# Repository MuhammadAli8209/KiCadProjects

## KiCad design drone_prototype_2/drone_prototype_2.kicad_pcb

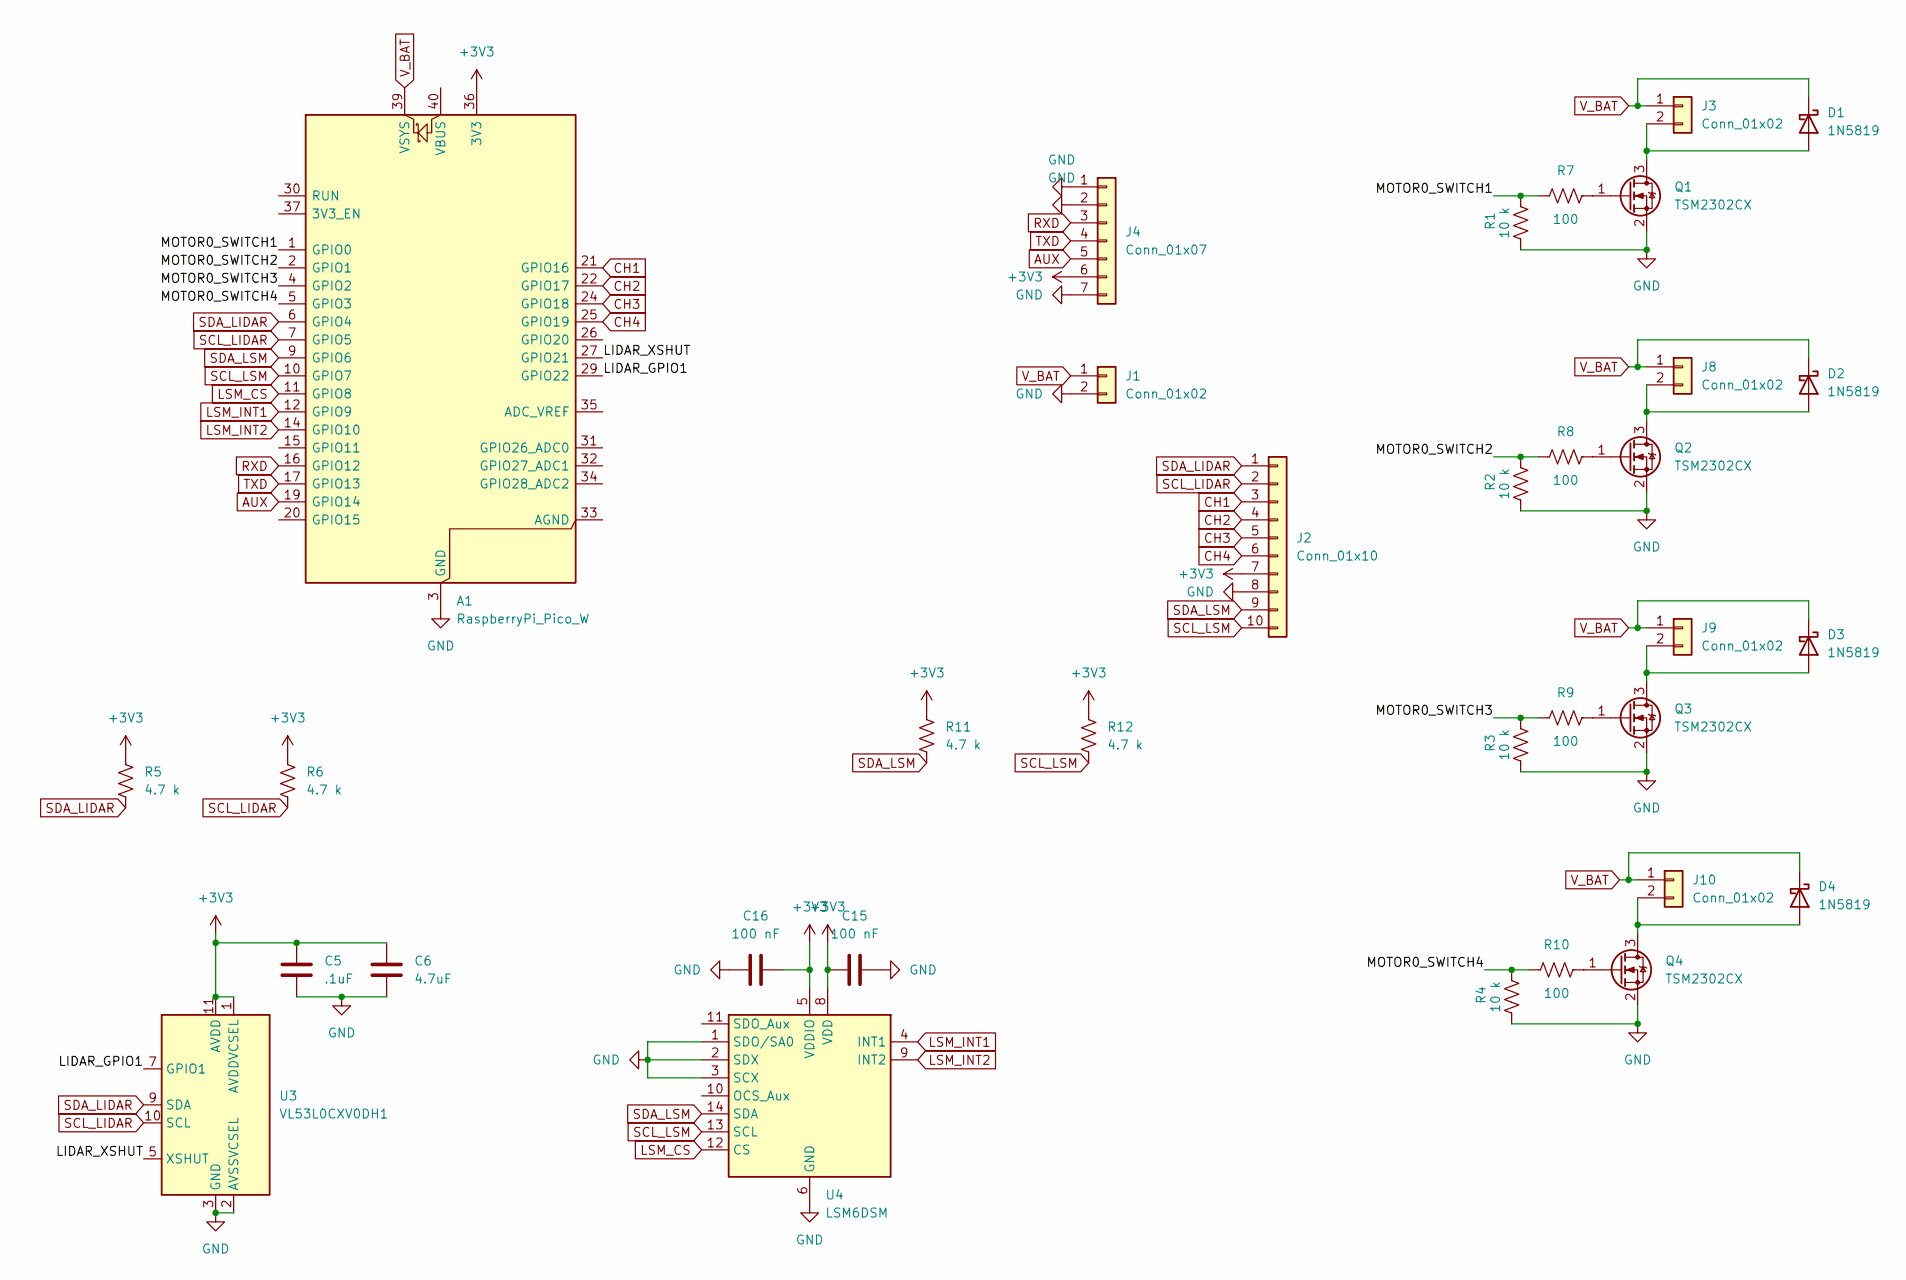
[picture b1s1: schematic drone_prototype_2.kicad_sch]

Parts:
A1: RaspberryPi_Pico_W; RaspberryPi_Pico_Common_Unspecified
C5: .1uF; C_0603_1608Metric
C6: 4.7uF; C_0603_1608Metric
C15, C16: 100 nF; C_0603_1608Metric
D1, D2, D3, D4: 1N5819; D_DO-41_SOD81_P10.16mm_Horizontal
J1, J3, J8, J9, J10: Conn_01x02; JST_PH_B2B-PH-K_1x02_P2.00mm_Vertical
J2: Conn_01x10; PinHeader_1x10_P2.54mm_Vertical
J4: Conn_01x07; PinHeader_1x07_P2.54mm_Vertical
Q1, Q2, Q3, Q4: TSM2302CX; SOT-23
R1, R2, R3, R4: 10 k; R_0603_1608Metric
R5, R6, R11, R12: 4.7 k; R_0603_1608Metric
R7, R8, R9, R10: 100; R_0603_1608Metric
U3: VL53L0CXV0DH1; ST_VL53L1x
U4: LSM6DSM; LGA-14_3x2.5mm_P0.5mm_LayoutBorder3x4y

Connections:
+3V3: A1.36 (3V3), C5.1, C6.1, C15.1, C16.2, J2.7, J4.6, R5.1, R6.1, R11.1, R12.1, U3.1 (AVDDVCSEL), U3.11 (AVDD), U4.5 (VDDIO), U4.8 (VDD)
/LIDAR_GPIO1: A1.29 (GPIO22), U3.7 (GPIO1)
/LIDAR_XSHUT: A1.27 (GPIO21), U3.5 (XSHUT)
/MOTOR0_SWITCH1: A1.1 (GPIO0), R1.2, R7.1
/MOTOR0_SWITCH2: A1.2 (GPIO1), R2.2, R8.1
/MOTOR0_SWITCH3: A1.4 (GPIO2), R3.2, R9.1
/MOTOR0_SWITCH4: A1.5 (GPIO3), R4.2, R10.1
AUX: A1.19 (GPIO14), J4.5
CH1: A1.21 (GPIO16), J2.3
CH2: A1.22 (GPIO17), J2.4
CH3: A1.24 (GPIO18), J2.5
CH4: A1.25 (GPIO19), J2.6
GND: A1.3 (GND), A1.8 (GND), A1.13 (GND), A1.18 (GND), A1.23 (GND), A1.28 (GND), A1.38 (GND), C5.2, C6.2, C15.2, C16.1, J1.2, J2.8, J4.1, J4.2, J4.7, Q1.2 (S), Q2.2 (S), Q3.2 (S), Q4.2 (S), R1.1, R2.1, R3.1, R4.1, U3.2 (AVSSVCSEL), U3.3 (GND), U3.4 (GND), U3.6 (GND), U3.12 (GND), U4.1 (SDO/SA0), U4.2 (SDX), U4.3 (SCX), U4.6 (GND), U4.7 (GND)
LSM_CS: A1.11 (GPIO8), U4.12 (CS)
LSM_INT1: A1.12 (GPIO9), U4.4 (INT1)
LSM_INT2: A1.14 (GPIO10), U4.9 (INT2)
unnamed: D1.2 (A), J3.2, Q1.3 (D)
unnamed: D2.2 (A), J8.2, Q2.3 (D)
unnamed: D3.2 (A), J9.2, Q3.3 (D)
unnamed: D4.2 (A), J10.2, Q4.3 (D)
unnamed: Q1.1 (G), R7.2
unnamed: Q2.1 (G), R8.2
unnamed: Q3.1 (G), R9.2
unnamed: Q4.1 (G), R10.2
RXD: A1.16 (GPIO12), J4.3
SCL_LIDAR: A1.7 (GPIO5), J2.2, R6.2, U3.10 (SCL)
SCL_LSM: A1.10 (GPIO7), J2.10, R12.2, U4.13 (SCL)
SDA_LIDAR: A1.6 (GPIO4), J2.1, R5.2, U3.9 (SDA)
SDA_LSM: A1.9 (GPIO6), J2.9, R11.2, U4.14 (SDA)
TXD: A1.17 (GPIO13), J4.4
V_BAT: A1.39 (VSYS), D1.1 (K), D2.1 (K), D3.1 (K), D4.1 (K), J1.1, J3.1, J8.1, J9.1, J10.1

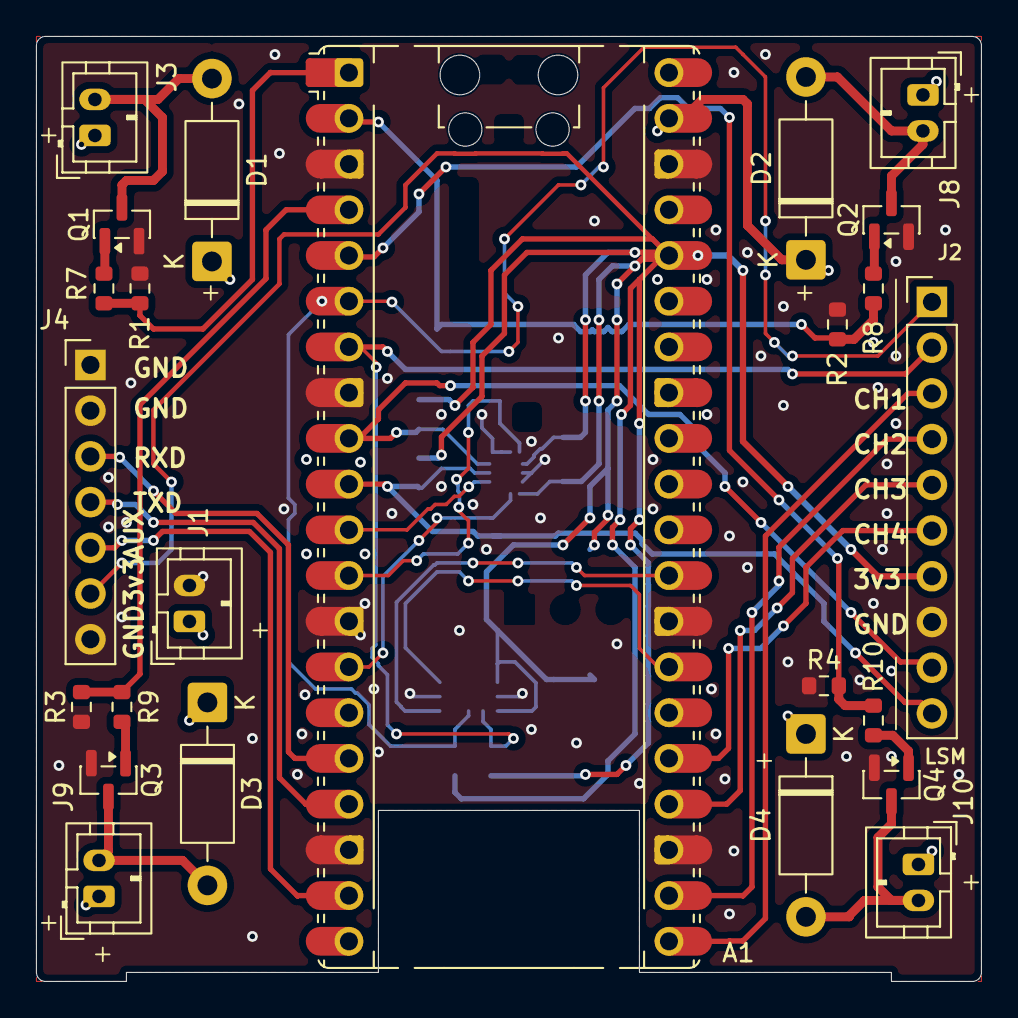
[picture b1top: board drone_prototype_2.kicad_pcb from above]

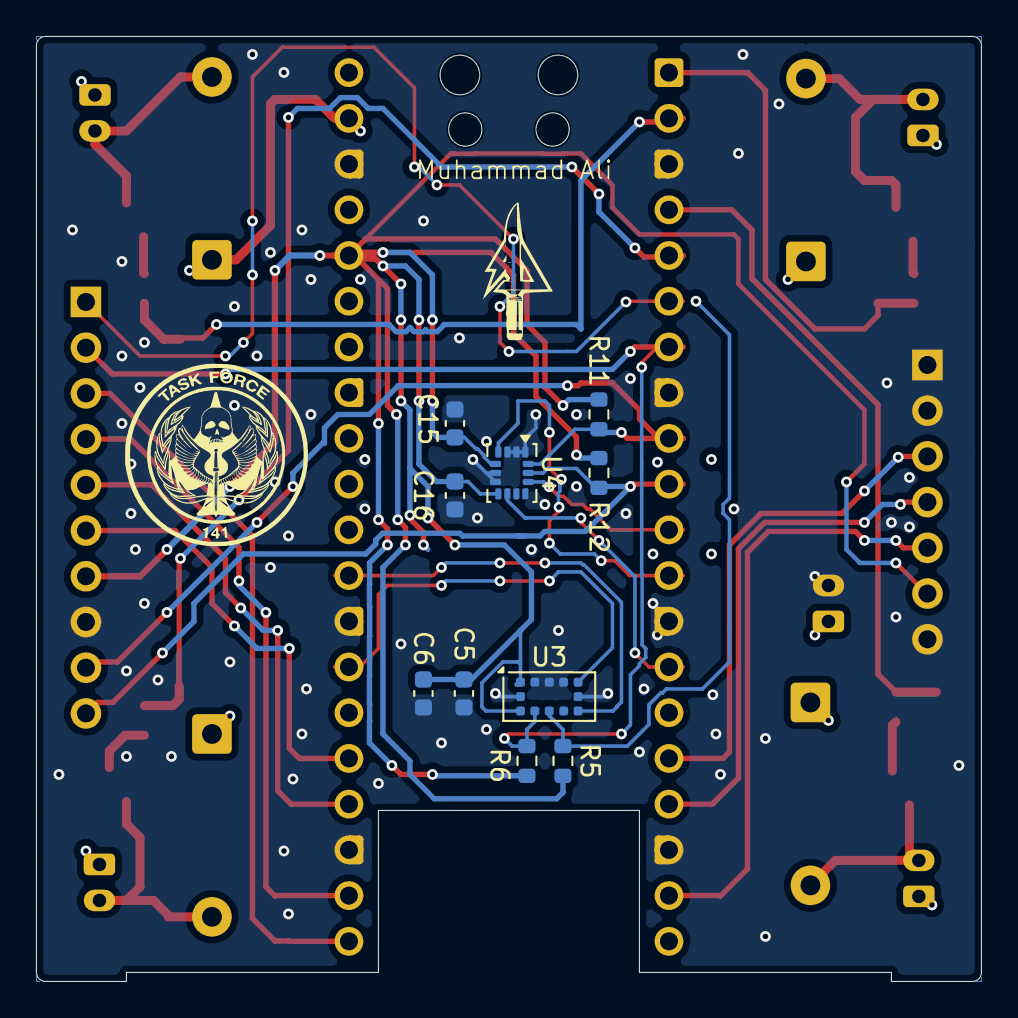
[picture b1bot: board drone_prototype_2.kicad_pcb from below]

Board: 4 copper layers, 52.5 x 52.5 mm, 34 parts (10 on the bottom side), 31 nets.

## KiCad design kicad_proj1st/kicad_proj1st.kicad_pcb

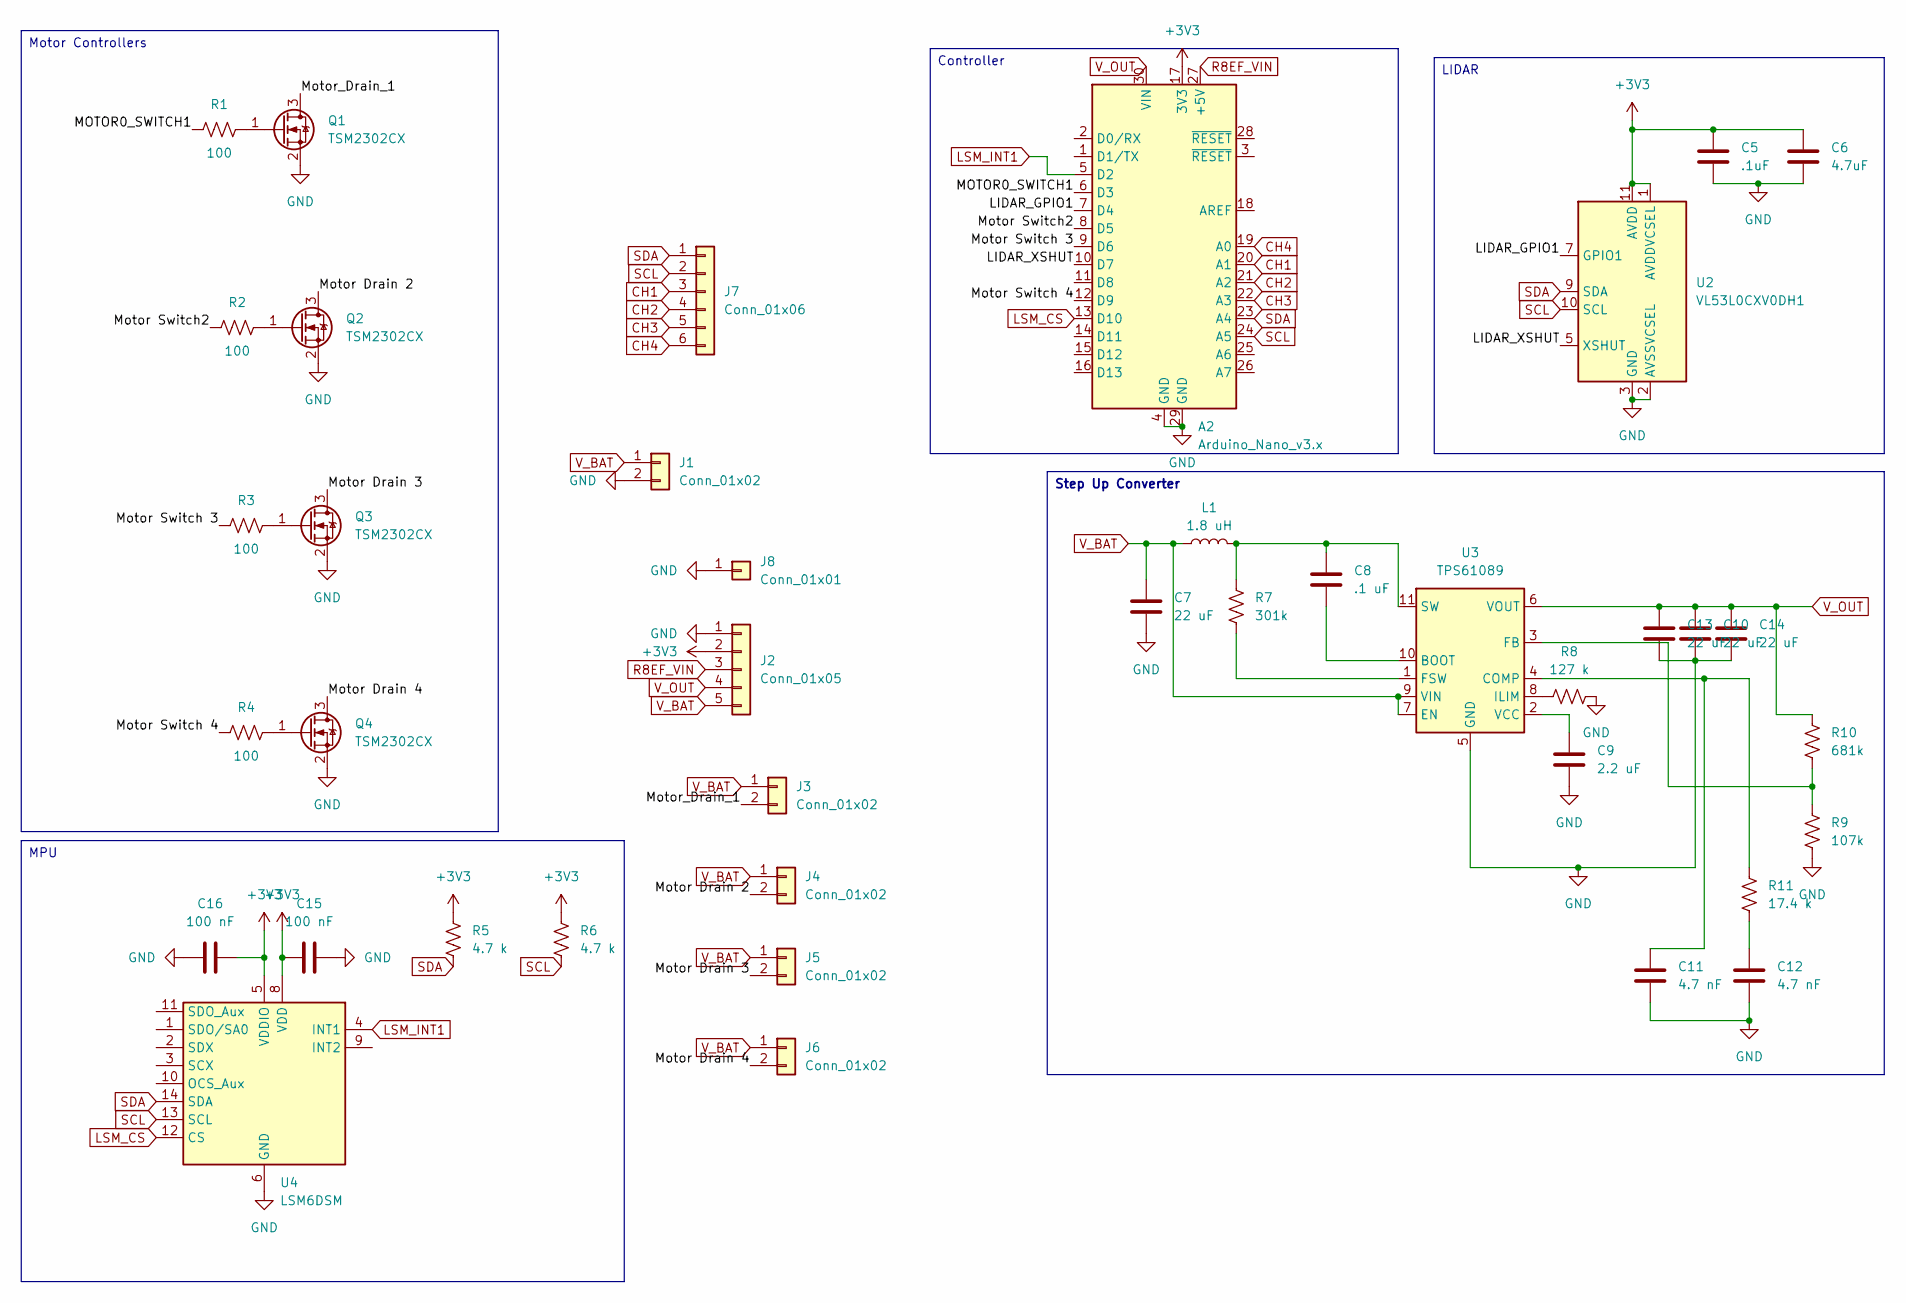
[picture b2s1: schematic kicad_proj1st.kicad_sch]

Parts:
A2: Arduino_Nano_v3.x; Arduino_Nano
C5: .1uF; C_0603_1608Metric
C6: 4.7uF; C_0603_1608Metric
C7, C10, C13, C14: 22 uF; C_0603_1608Metric
C8: .1 uF; C_0603_1608Metric
C9: 2.2 uF; C_0603_1608Metric
C11, C12: 4.7 nF; C_0603_1608Metric
C15, C16: 100 nF; C_0603_1608Metric
J1, J3, J4, J5, J6: Conn_01x02; JST_PH_B2B-PH-K_1x02_P2.00mm_Vertical
J2: Conn_01x05; PinHeader_1x05_P2.54mm_Vertical
J7: Conn_01x06; PinHeader_1x06_P2.54mm_Vertical
J8: Conn_01x01; PinHeader_1x01_P2.54mm_Vertical
L1: 1.8 uH; L_Sumida_CDMC6D28_7.25x6.5mm
Q1, Q2, Q3, Q4: TSM2302CX; SOT-23
R1, R2, R3, R4: 100; R_0603_1608Metric
R5, R6: 4.7 k; R_0603_1608Metric
R7: 301k; R_0603_1608Metric
R8: 127 k; R_0603_1608Metric
R9: 107k; R_0603_1608Metric
R10: 681k; R_0603_1608Metric
R11: 17.4 k; R_0603_1608Metric
U2: VL53L0CXV0DH1; ST_VL53L1x
U3: TPS61089; Texas_VQFN-RNR0011A-11
U4: LSM6DSM; LGA-14_3x2.5mm_P0.5mm_LayoutBorder3x4y

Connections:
+3V3: A2.17 (3V3), C5.1, C6.1, C15.1, C16.2, J2.2, R5.1, R6.1, U2.1 (AVDDVCSEL), U2.11 (AVDD), U4.5 (VDDIO), U4.8 (VDD)
/LIDAR_GPIO1: A2.7 (D4), U2.7 (GPIO1)
/LIDAR_XSHUT: A2.10 (D7), U2.5 (XSHUT)
/MOTOR0_SWITCH1: A2.6 (D3), R1.1
/Motor Drain 2: J4.2, Q2.3 (D)
/Motor Drain 3: J5.2, Q3.3 (D)
/Motor Drain 4: J6.2, Q4.3 (D)
/Motor Switch2: A2.8 (D5), R2.1
/Motor Switch 3: A2.9 (D6), R3.1
/Motor Switch 4: A2.12 (D9), R4.1
/Motor_Drain_1: J3.2, Q1.3 (D)
CH1: A2.20 (A1), J7.3
CH2: A2.21 (A2), J7.4
CH3: A2.22 (A3), J7.5
CH4: A2.19 (A0), J7.6
GND: A2.4 (GND), A2.29 (GND), C5.2, C6.2, C7.2, C9.2, C10.2, C11.2, C12.2, C13.2, C14.2, C15.2, C16.1, J1.2, J2.1, J8.1, Q1.2 (S), Q2.2 (S), Q3.2 (S), Q4.2 (S), R8.2, R9.2, U2.2 (AVSSVCSEL), U2.3 (GND), U2.4 (GND), U2.6 (GND), U2.12 (GND), U3.5 (GND), U4.6 (GND), U4.7 (GND)
LSM_CS: A2.13 (D10), U4.12 (CS)
LSM_INT1: A2.5 (D2), U4.4 (INT1)
unnamed: C12.1, R11.2
unnamed: Q1.1 (G), R1.2
unnamed: Q2.1 (G), R2.2
unnamed: Q3.1 (G), R3.2
unnamed: Q4.1 (G), R4.2
unnamed: C8.2, U3.10 (BOOT)
unnamed: C11.1, R11.1, U3.4 (COMP)
unnamed: R9.1, R10.2, U3.3 (FB)
unnamed: R7.2, U3.1 (FSW)
unnamed: R8.1, U3.8 (ILIM)
unnamed: C8.1, L1.2, R7.1, U3.11 (SW)
unnamed: C9.1, U3.2 (VCC)
R8EF_VIN: A2.27 (+5V), J2.3
SCL: A2.24 (A5), J7.2, R6.2, U2.10 (SCL), U4.13 (SCL)
SDA: A2.23 (A4), J7.1, R5.2, U2.9 (SDA), U4.14 (SDA)
V_BAT: C7.1, J1.1, J2.5, J3.1, J4.1, J5.1, J6.1, L1.1, U3.7 (EN), U3.9 (VIN)
V_OUT: A2.30 (VIN), C10.1, C13.1, C14.1, J2.4, R10.1, U3.6 (VOUT)

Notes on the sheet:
Step Up Converter
Controller
MPU
LIDAR
Motor Controllers

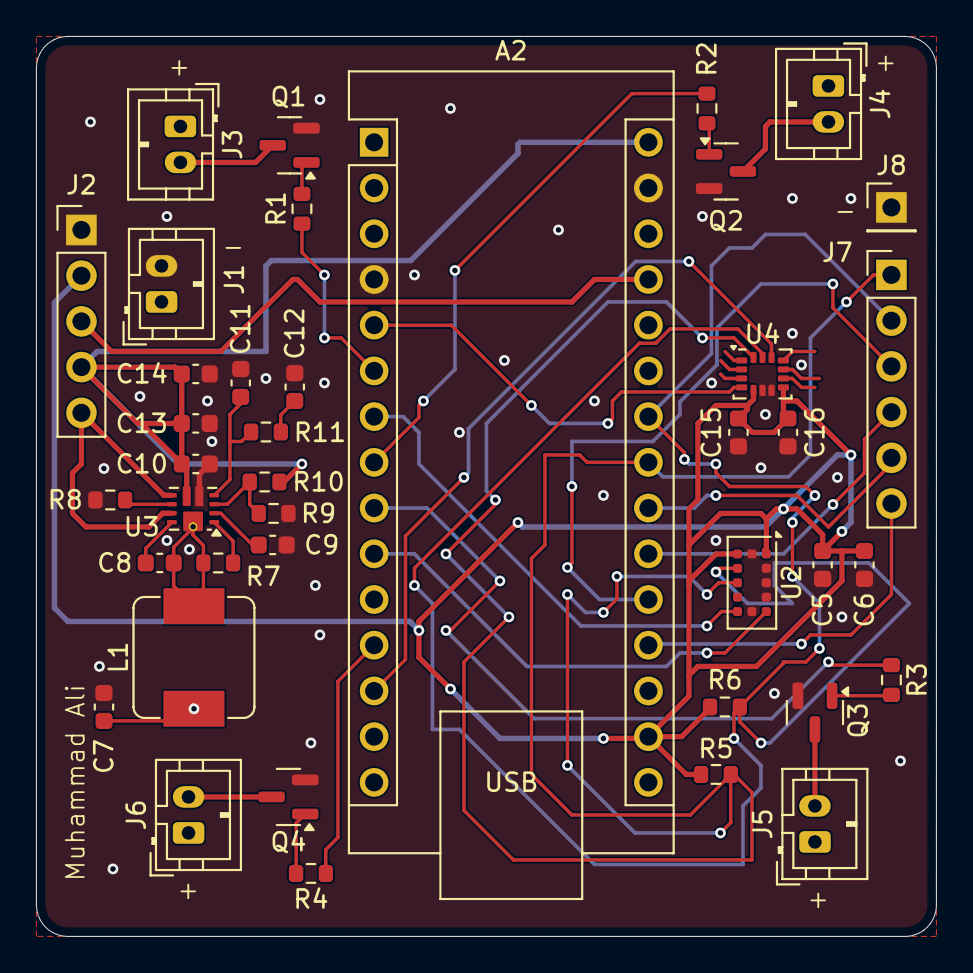
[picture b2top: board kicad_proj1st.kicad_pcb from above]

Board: 4 copper layers, 50.0 x 50.0 mm, 40 parts (0 on the bottom side), 35 nets.

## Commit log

2026-02-02 pushing
2026-02-07 Prototype 2 fin?
2026-02-16 please please i need to order this
2026-02-16 ok ok las push pls pls i ned to order
2026-02-16 ok ok real las push pls pls i ned to order
2026-06-27 drone_prototype_2
